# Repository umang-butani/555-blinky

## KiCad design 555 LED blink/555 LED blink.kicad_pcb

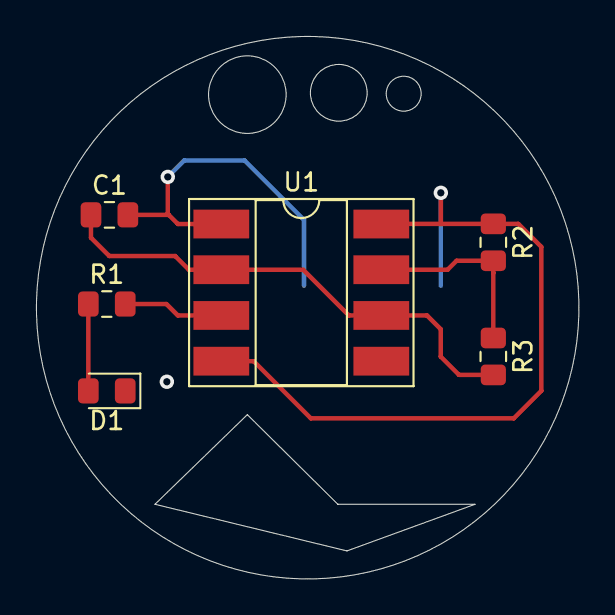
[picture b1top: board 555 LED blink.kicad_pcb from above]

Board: 2 copper layers, 30.1 x 30.1 mm, 7 parts (1 on the bottom side), 6 nets.

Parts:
BT1: Battery_Cell; BatteryHolder_LINX_BAT-HLD-012-SMT
C1: C; C_0805_2012Metric_Pad1.15x1.40mm_HandSolder
D1: LED; LED_0805_2012Metric_Pad1.15x1.40mm_HandSolder
R1, R2, R3: R; R_0805_2012Metric_Pad1.15x1.40mm_HandSolder
U1: LM555; DIP-8_W8.89mm_SMDSocket_LongPads

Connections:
GND: BT1.2, C1.2, D1.1, U1.1
unnamed: BT1.1, R2.1, U1.4, U1.8
unnamed: C1.1, R3.2, U1.2, U1.6
unnamed: D1.2, R1.1
unnamed: R1.2, U1.3
unnamed: R2.2, R3.1, U1.7

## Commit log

2019-10-15 Complited all files
